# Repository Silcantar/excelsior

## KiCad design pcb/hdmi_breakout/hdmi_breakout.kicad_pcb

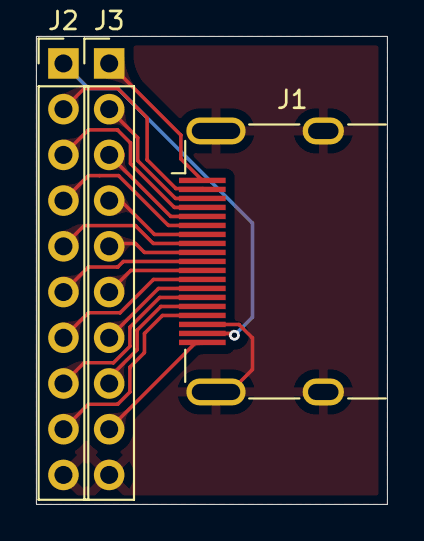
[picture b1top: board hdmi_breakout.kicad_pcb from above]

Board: 2 copper layers, 19.5 x 26.0 mm, 3 parts (0 on the bottom side), 19 nets.

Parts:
J1: HDMI_C_1.4; HDMI_A_Molex_208658-1001_Horizontal
J2, J3: Conn_01x10; PinHeader_1x10_P2.54mm_Vertical

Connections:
/GND: J1.17 (GND), J1.SH, J2.10, J3.10
/P01: J1.1 (D2+), J3.1
/P02: J1.2 (D2S), J2.2
/P03: J1.3 (D2-), J3.2
/P04: J1.4 (D1+), J2.3
/P05: J1.5 (D1S), J3.3
/P06: J1.6 (D1-), J2.4
/P07: J1.7 (D0+), J3.4
/P08: J1.8 (D0S), J2.5
/P09: J1.9 (D0-), J3.5
/P10: J1.10 (CK+), J2.6
/P11: J1.11 (CKS), J3.6
/P12: J1.12 (CK-), J2.7
/P13: J1.13 (CEC), J3.7
/P14: J1.14 (UTILITY/HEAC+), J2.8
/P15: J1.15 (SCL), J3.8
/P16: J1.16 (SDA), J2.9
/P19: J1.19 (HPD/HEAC-), J3.9
/VBUS: J1.18 (+5V), J2.1
